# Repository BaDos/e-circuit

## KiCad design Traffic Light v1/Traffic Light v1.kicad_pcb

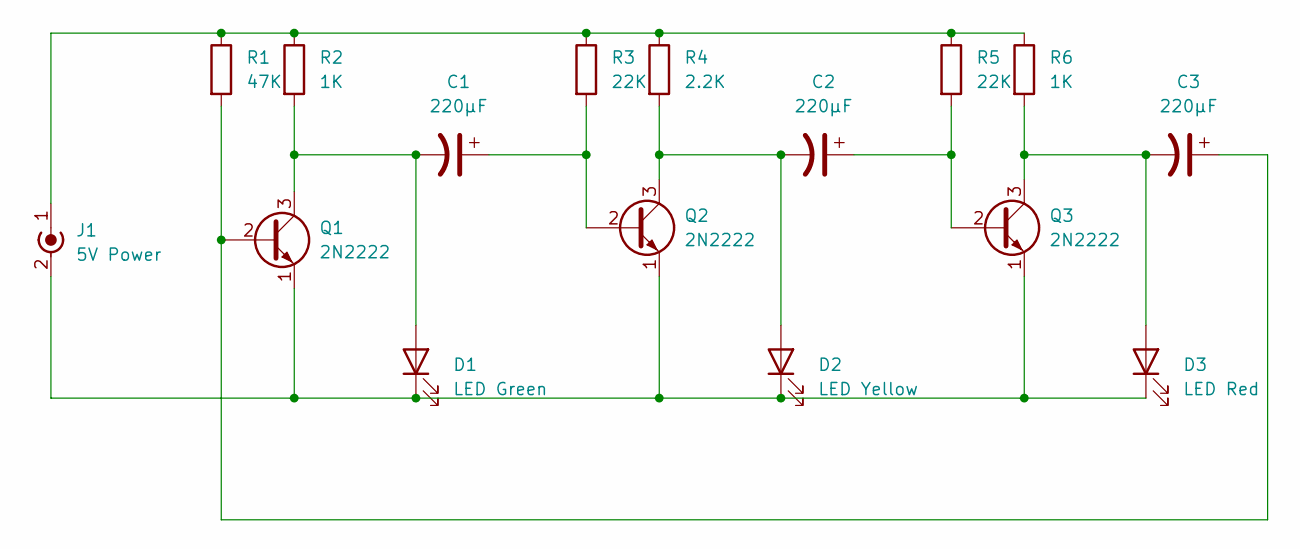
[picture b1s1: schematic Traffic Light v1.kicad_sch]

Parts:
C1, C2, C3: 220µF; CP_Radial_D5.0mm_P2.50mm
D1: LED Green; LED_D5.0mm
D2: LED Yellow; LED_D5.0mm
D3: LED Red; LED_D5.0mm
J1: 5V Power; Molex_Mini-Fit_Jr_5566-02A_2x01_P4.20mm_Vertical
Q1, Q2, Q3: 2N2222; TO-92L_Inline
R1: 47K; R_Axial_DIN0204_L3.6mm_D1.6mm_P7.62mm_Horizontal
R2, R6: 1K; R_Axial_DIN0204_L3.6mm_D1.6mm_P7.62mm_Horizontal
R3, R5: 22K; R_Axial_DIN0204_L3.6mm_D1.6mm_P7.62mm_Horizontal
R4: 2.2K; R_Axial_DIN0204_L3.6mm_D1.6mm_P7.62mm_Horizontal

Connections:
unnamed: C1.1, Q2.2 (B), R3.2
unnamed: C1.2, D1.2 (A), Q1.3 (C), R2.2
unnamed: C2.1, Q3.2 (B), R5.2
unnamed: C2.2, D2.2 (A), Q2.3 (C), R4.2
unnamed: C3.1, Q1.2 (B), R1.2
unnamed: C3.2, D3.2 (A), Q3.3 (C), R6.2
unnamed: D1.1 (K), D2.1 (K), D3.1 (K), J1.2 (Ext), Q1.1 (E), Q2.1 (E), Q3.1 (E)
unnamed: J1.1 (In), R1.1, R2.1, R3.1, R4.1, R5.1, R6.1

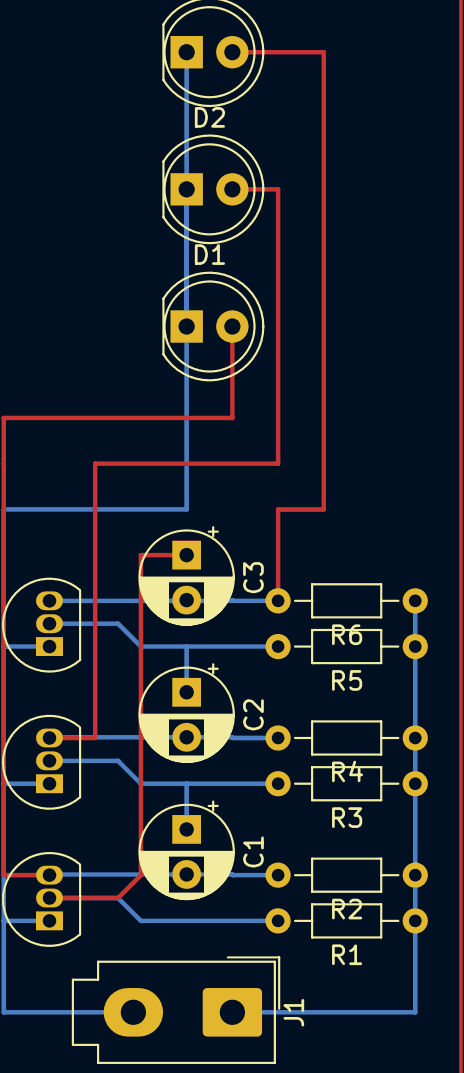
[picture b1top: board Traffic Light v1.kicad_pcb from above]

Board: 2 copper layers, 16 parts (0 on the bottom side), 8 nets.

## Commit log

2022-01-17 Traffic light v1
